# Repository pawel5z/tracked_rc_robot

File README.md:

# tracked_rc_robot

Tracked robot prototype with bluetooth remote control, using [Dabble app](https://thestempedia.com/docs/dabble/game-pad-module/)'s gamepad module.

## Demo

## Components

* [Black Gladiator - Tracked Robot Chassis](https://www.dfrobot.com/product-1860.html)
* Raspberry Pi Pico
* HC-05 bluetooth module
* 2 x L293D motor driver
* L7805 voltage regulator
* tact switch 6x6mm THT
* 2 x capacitor 1µF
* 3 x capacitor 100nF
* capacitor 330nF
* 2 x Li-ion 18650 3.7V 2200mAh cell

## Notes

[Board layout](https://github.com/pawel5z/tracked_rc_robot/blob/main/circuit/stripboard.diy) created with [DIY Layout Creator](http://diy-fever.com/software/diylc/).

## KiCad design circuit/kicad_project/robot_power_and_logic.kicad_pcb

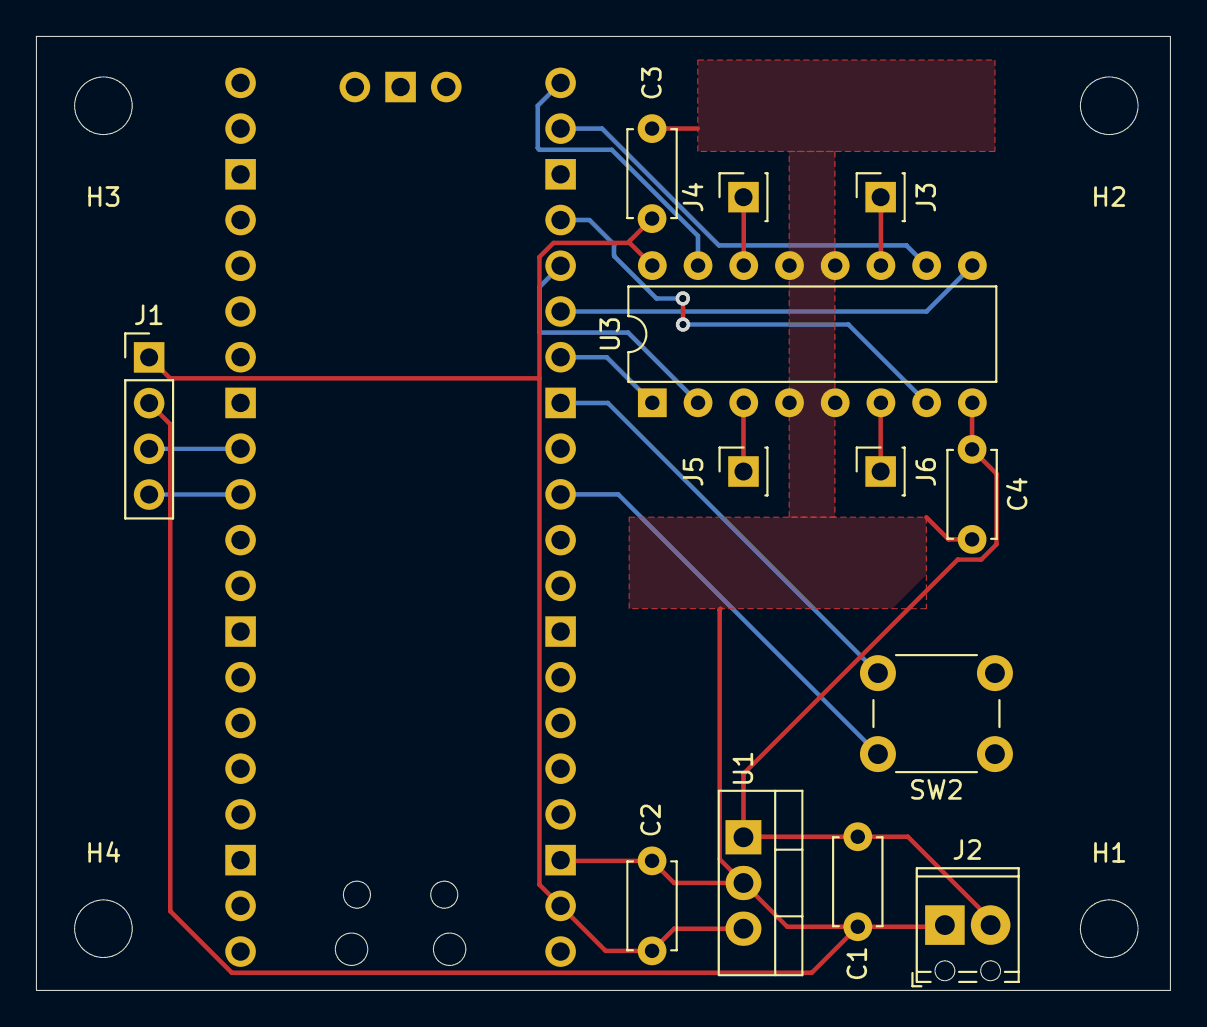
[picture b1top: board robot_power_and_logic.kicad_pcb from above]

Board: 2 copper layers, 63.0 x 53.0 mm, 18 parts (1 on the bottom side), 17 nets.

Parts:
C1: 330 nF; C_Disc_D4.7mm_W2.5mm_P5.00mm
C2, C3: 100 nF; C_Disc_D4.7mm_W2.5mm_P5.00mm
C4: 1 µF; C_Disc_D4.7mm_W2.5mm_P5.00mm
H1, H2, H3, H4: MountingHole; MountingHole_3.2mm_M3
J1: HC-05 connection socket; PinHeader_1x04_P2.54mm_Vertical
J2: Power terminal; TerminalBlock_Phoenix_MPT-0,5-2-2.54_1x02_P2.54mm_Horizontal
J3: right_track_motor+; PinSocket_1x01_P2.54mm_Vertical
J4: right_track_motor-; PinSocket_1x01_P2.54mm_Vertical
J5: left_track_motor+; PinSocket_1x01_P2.54mm_Vertical
J6: left_track_motor-; PinSocket_1x01_P2.54mm_Vertical
SW2: Reset; SW_PUSH_6mm_H4.3mm
U1: LM7805_TO220; TO-220-3_Vertical
U2: Pico; RPi_Pico_SMD_TH
U3: L293D; DIP-16_W7.62mm

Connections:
/+5V: C2.1, C3.2, J1.1, U1.3 (VO), U2.39 (VSYS), U3.16 (VCC1)
/+7.4V: C1.1, C4.2, J2.2, U1.1 (VI), U3.8 (VCC2)
/GND: C1.2, C2.2, C3.1, C4.1, J1.2, J2.1, U1.2 (GND), U2.38 (GND), U3.4 (GND), U3.5 (GND), U3.12 (GND), U3.13 (GND)
/HC-05 RX: J1.4, U2.11 (GPIO8)
/HC-05 TX: J1.3, U2.12 (GPIO9)
/left_track_motor_ch_in_1: U2.25 (GPIO19), U3.2 (1A)
/left_track_motor_ch_in_2: U2.24 (GPIO18), U3.7 (2A)
/left_track_motor_en: U2.27 (GPIO21), U3.1 (EN1,2)
/right_track_motor_ch_in_1: U2.22 (GPIO17), U3.10 (3A)
/right_track_motor_ch_in_2: U2.21 (GPIO16), U3.15 (4A)
/right_track_motor_en: U2.26 (GPIO20), U3.9 (EN3,4)
unnamed: J3.1, U3.11 (3Y)
unnamed: J4.1, U3.14 (4Y)
unnamed: J5.1, U3.3 (1Y)
unnamed: J6.1, U3.6 (2Y)
unnamed: SW2.1, U2.30 (RUN)
unnamed: SW2.2, U2.28 (GND)

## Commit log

2022-08-31 Add circuit diagram and notes
2022-08-31 Add 2nd motor driver
2022-08-31 Remove previous circuit diagrams
    cause we have version control for keeping them.
2022-08-31 Add bypass capacitors to motor drivers
2022-08-31 Add HC-05 pinout
2022-09-01 Update HC-05 power connection
2022-09-01 Move circuit diagram files to separate directory
2022-09-01 Change UART pins used for communication with HC-05
2022-09-01 Add stripboard circuit diagram
2022-09-02 Add trace cuts under motor drivers
2022-09-04 Add initialization code
2022-09-04 Add steering logic
2022-09-04 Change HC-05 power source to Pico's 3V3 pin
2022-09-04 Add printing bt logs to file
2022-09-04 Add docstrings
2022-09-15 Lower bluetooth baud rate
2022-09-15 Fix joystick input interpretation
2022-09-15 Improve speed control
2022-09-17 Fix `None` value access in `Track` class
2022-09-21 Simplify `Track`'s power implementation
2022-09-22 Move MicroPython logic to separate directory
2022-09-22 Add `pico-sdk` submodule
2022-09-22 Set up basic C++ project with CMake
2022-09-23 Port MicroPython logic to C/C++
2022-09-24 Add docstrings
    and choose more descriptive name for bluetooth UART.
2022-09-24 Fix PWM setup and control
2022-09-24 Add comments to `handleJoystick` function
2022-09-24 Add demo, list components and change description
2022-09-26 Fix docstring of `Track` class
2022-09-30 Add board layout details to `README.md`
2022-09-30 Update board layout schematic
2023-02-05 Replace some wire connections with label connections
2023-02-05 Assign some footprints and add no-connection flags
2023-02-05 Add power symbols
2023-02-05 Align elements
2023-02-07 Assign capacitor footprints
2023-02-07 Add title, date and revision number
2023-02-07 Add L293D soldering info
2023-02-08 Replace spst reset switch with push button switch
2023-02-08 Fix Raspberry Pi Pico symbol
2023-02-08 Update reset button footprint
2023-02-08 Assign correct footprint to Raspberry Pi Pico
2023-02-08 Clean up power annotations
2023-02-08 Add screw terminal
2023-02-08 Add mounting holes and swap pins of screw terminal
2023-02-08 Replace some GND symbols with GND labels
2023-02-09 Replace motors with their connection sockets
2023-02-09 Update power source connection description
2023-02-09 Remove one L293D driver
2023-02-09 Create empty PCB design
2023-02-09 Create PCB elements layout
2023-02-09 Add routes to PCB design
